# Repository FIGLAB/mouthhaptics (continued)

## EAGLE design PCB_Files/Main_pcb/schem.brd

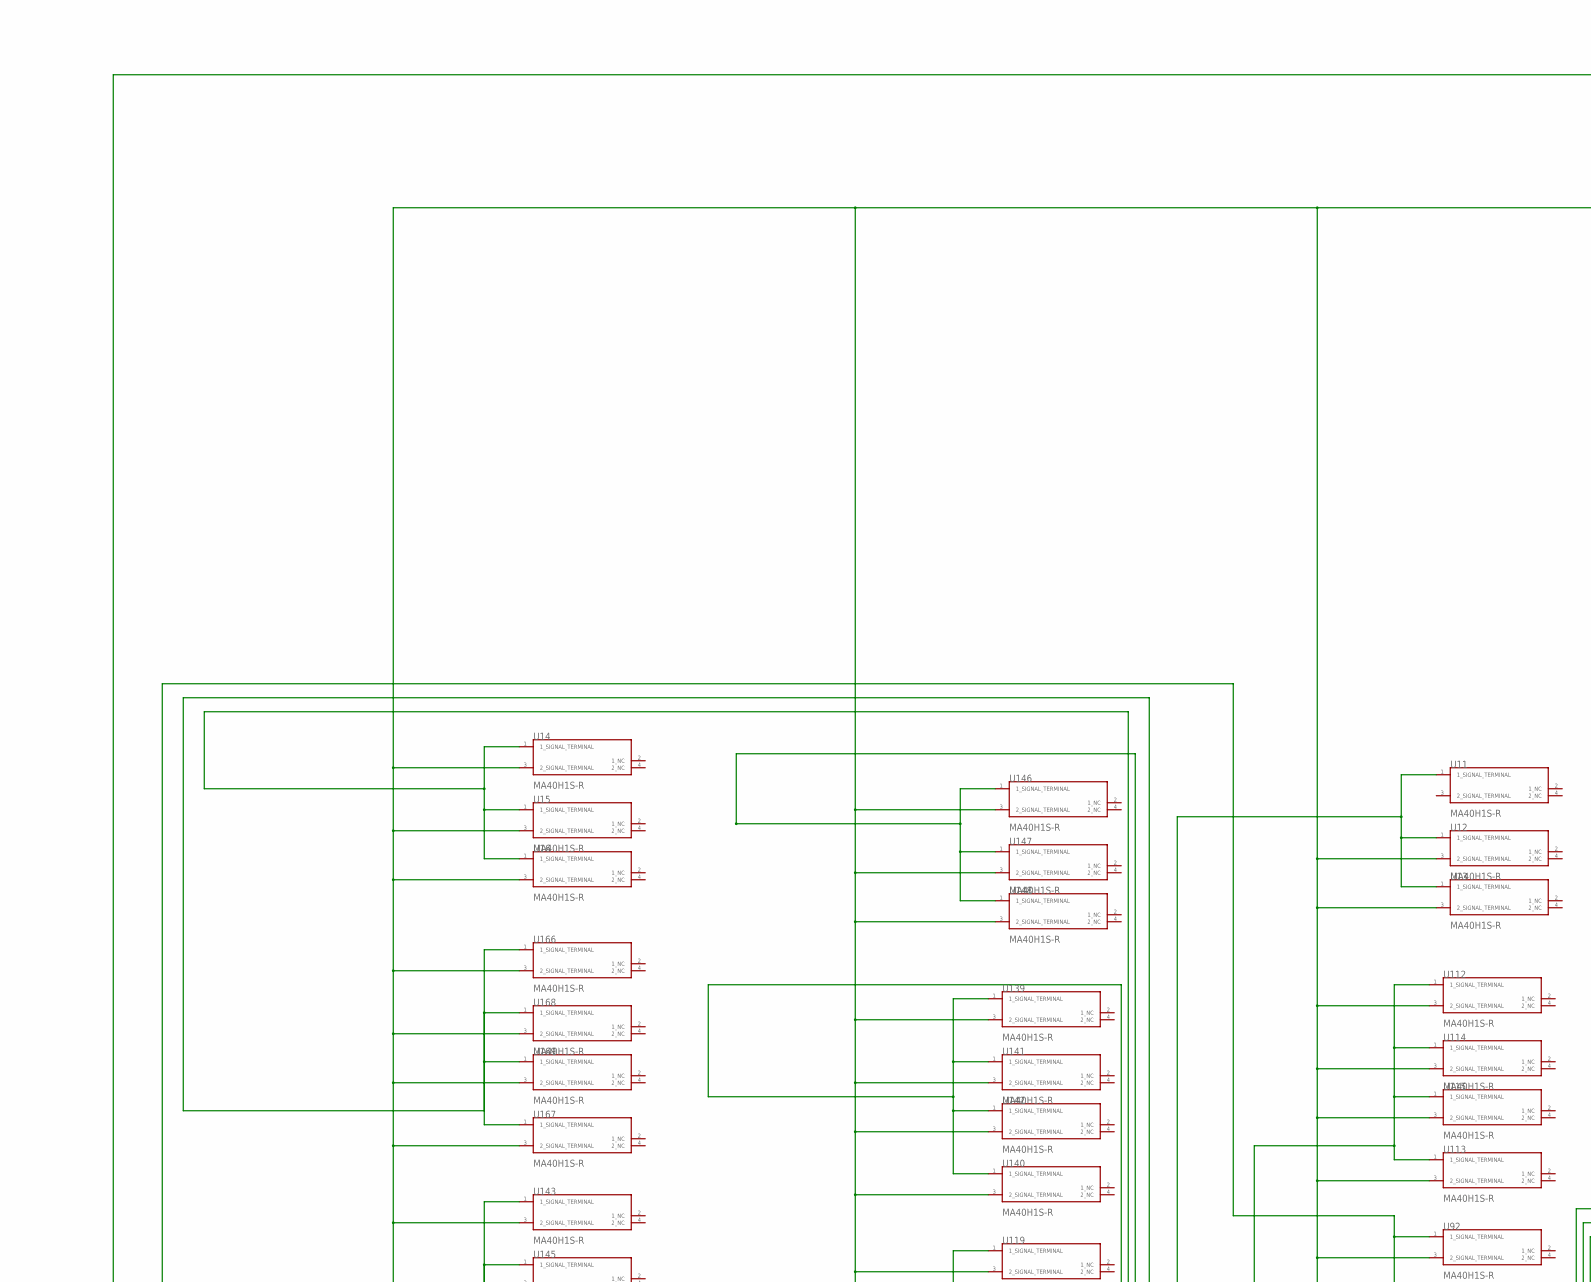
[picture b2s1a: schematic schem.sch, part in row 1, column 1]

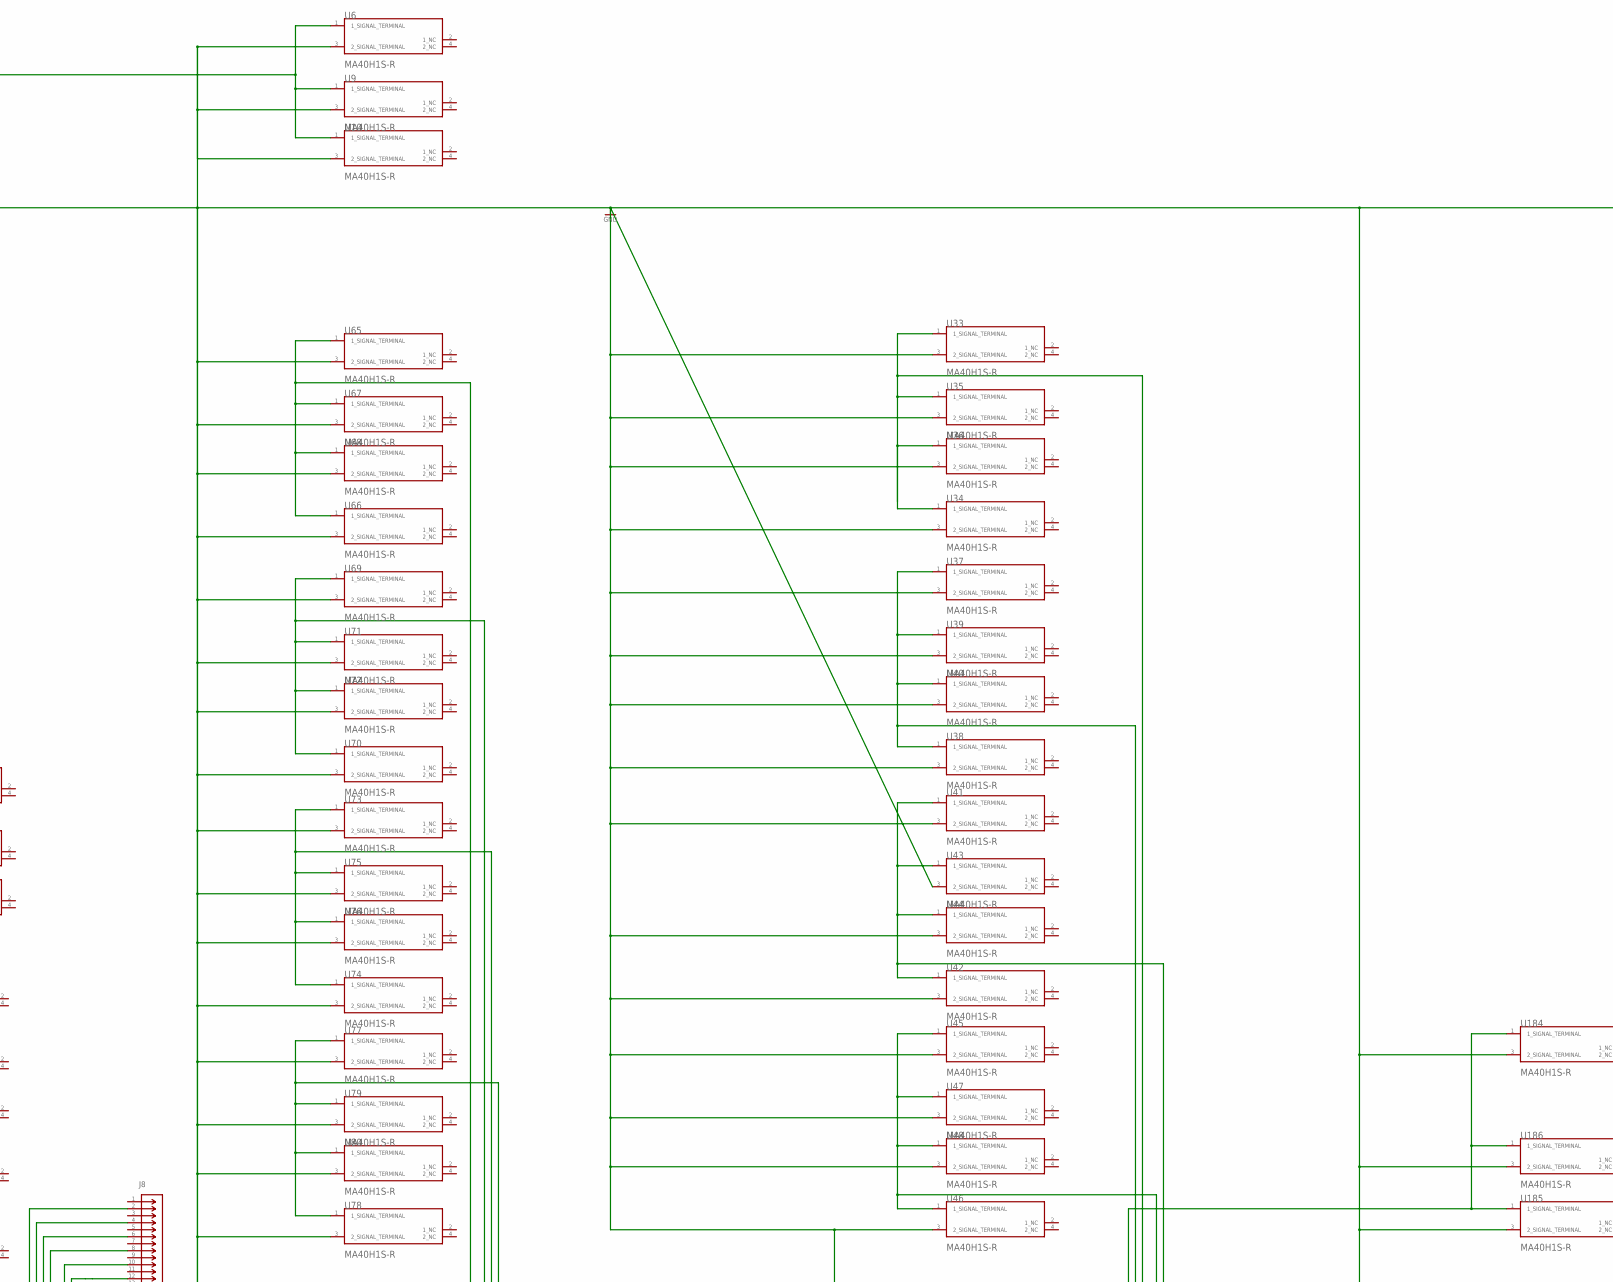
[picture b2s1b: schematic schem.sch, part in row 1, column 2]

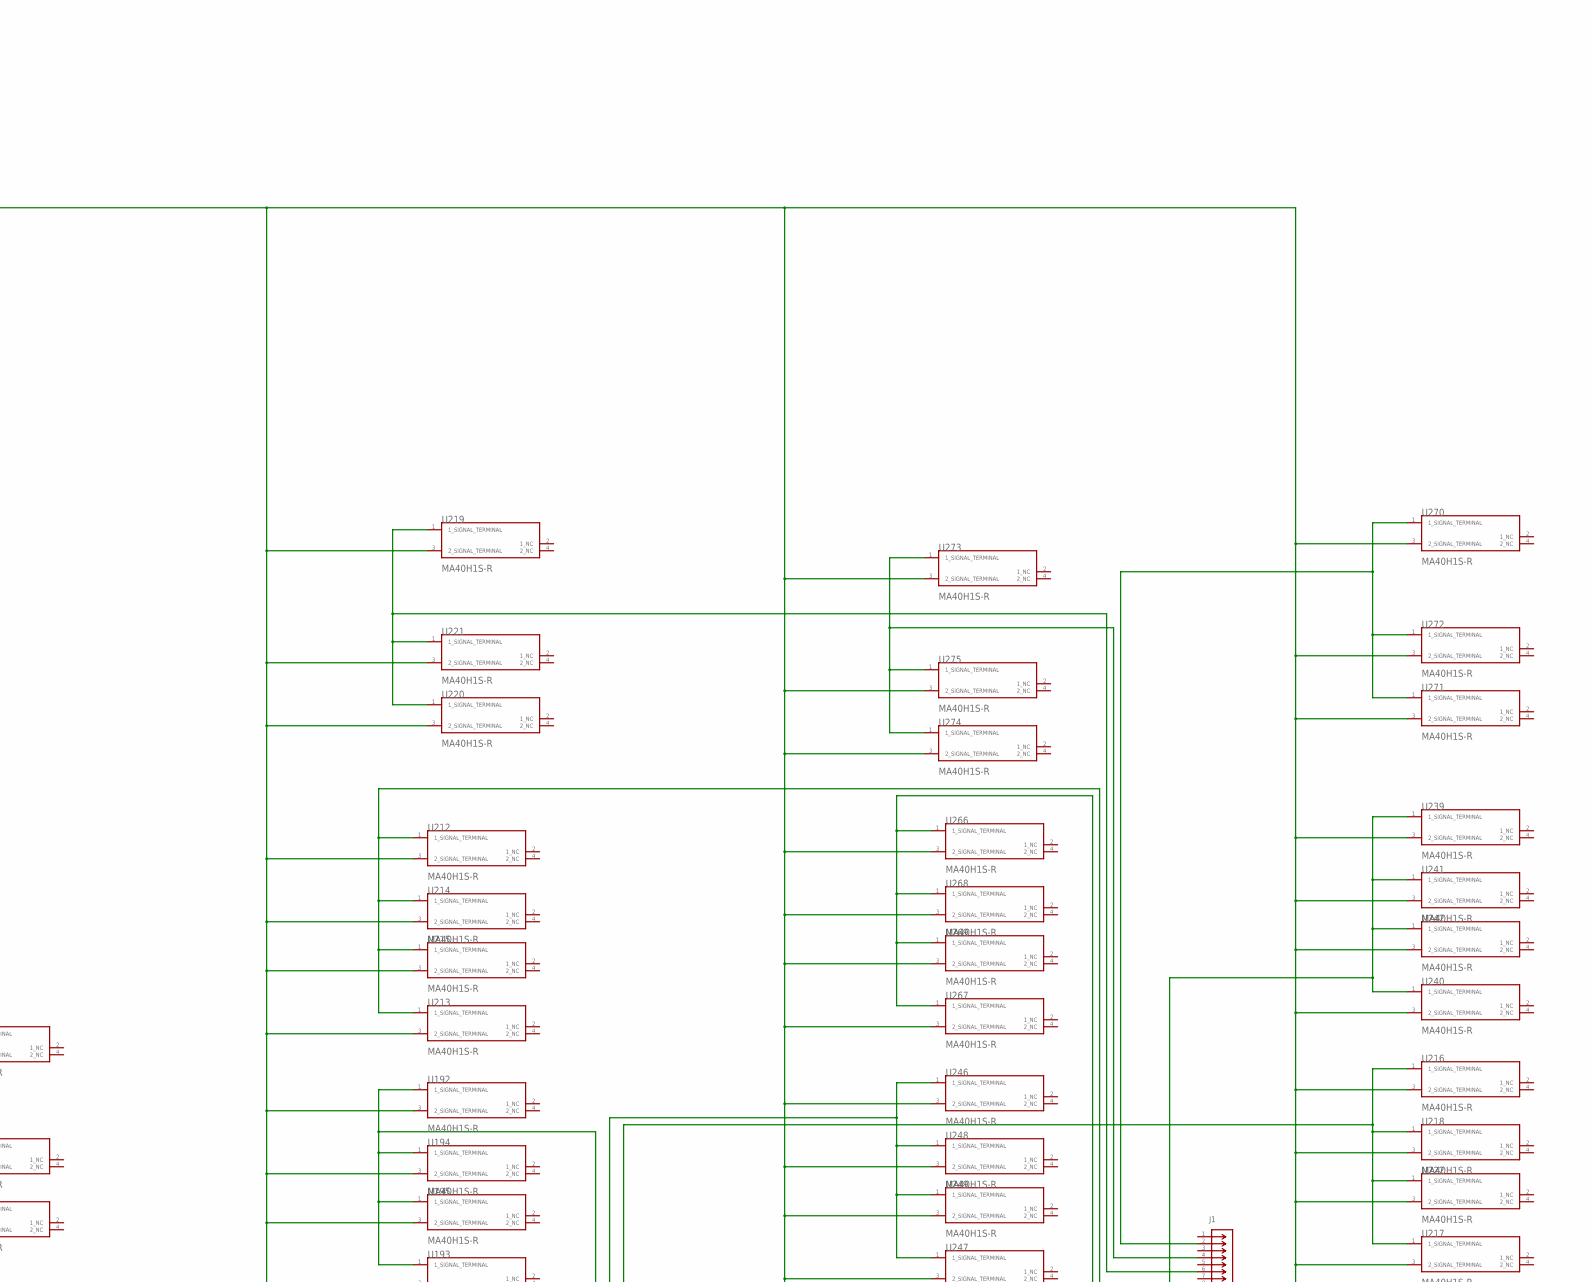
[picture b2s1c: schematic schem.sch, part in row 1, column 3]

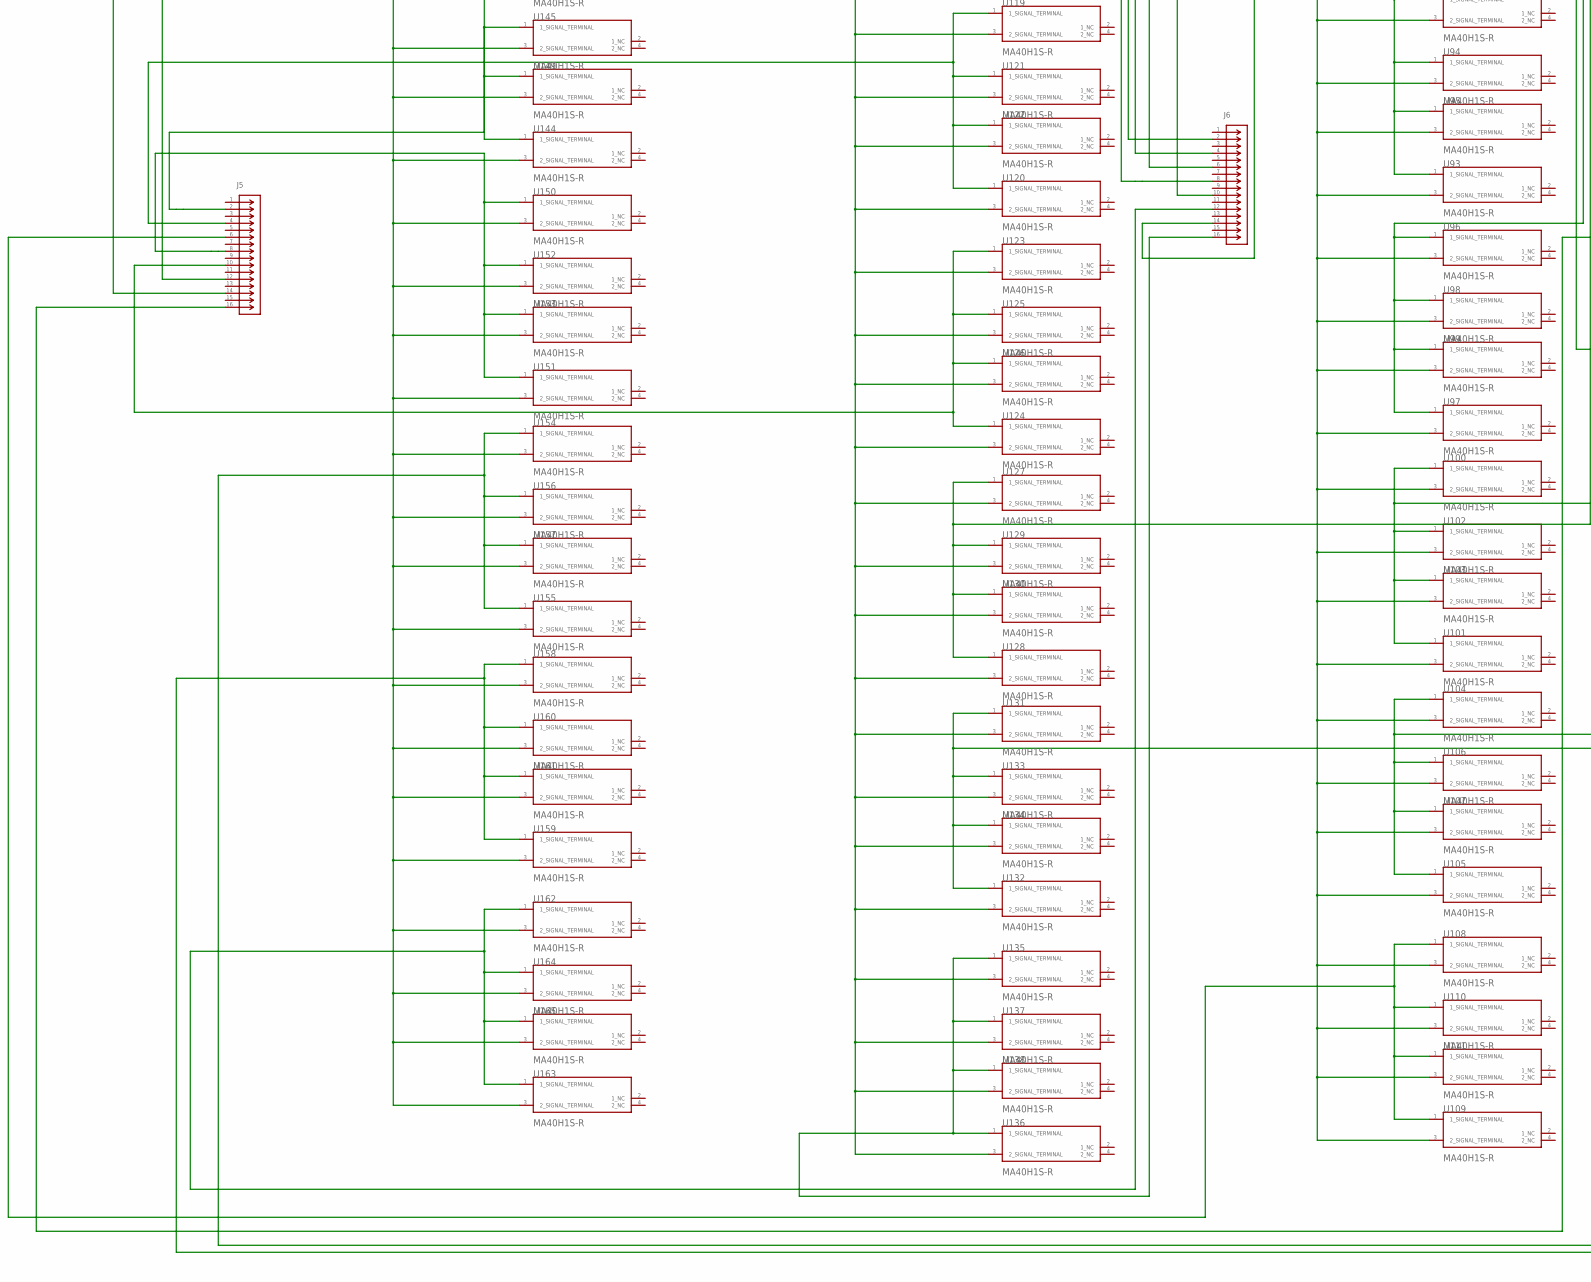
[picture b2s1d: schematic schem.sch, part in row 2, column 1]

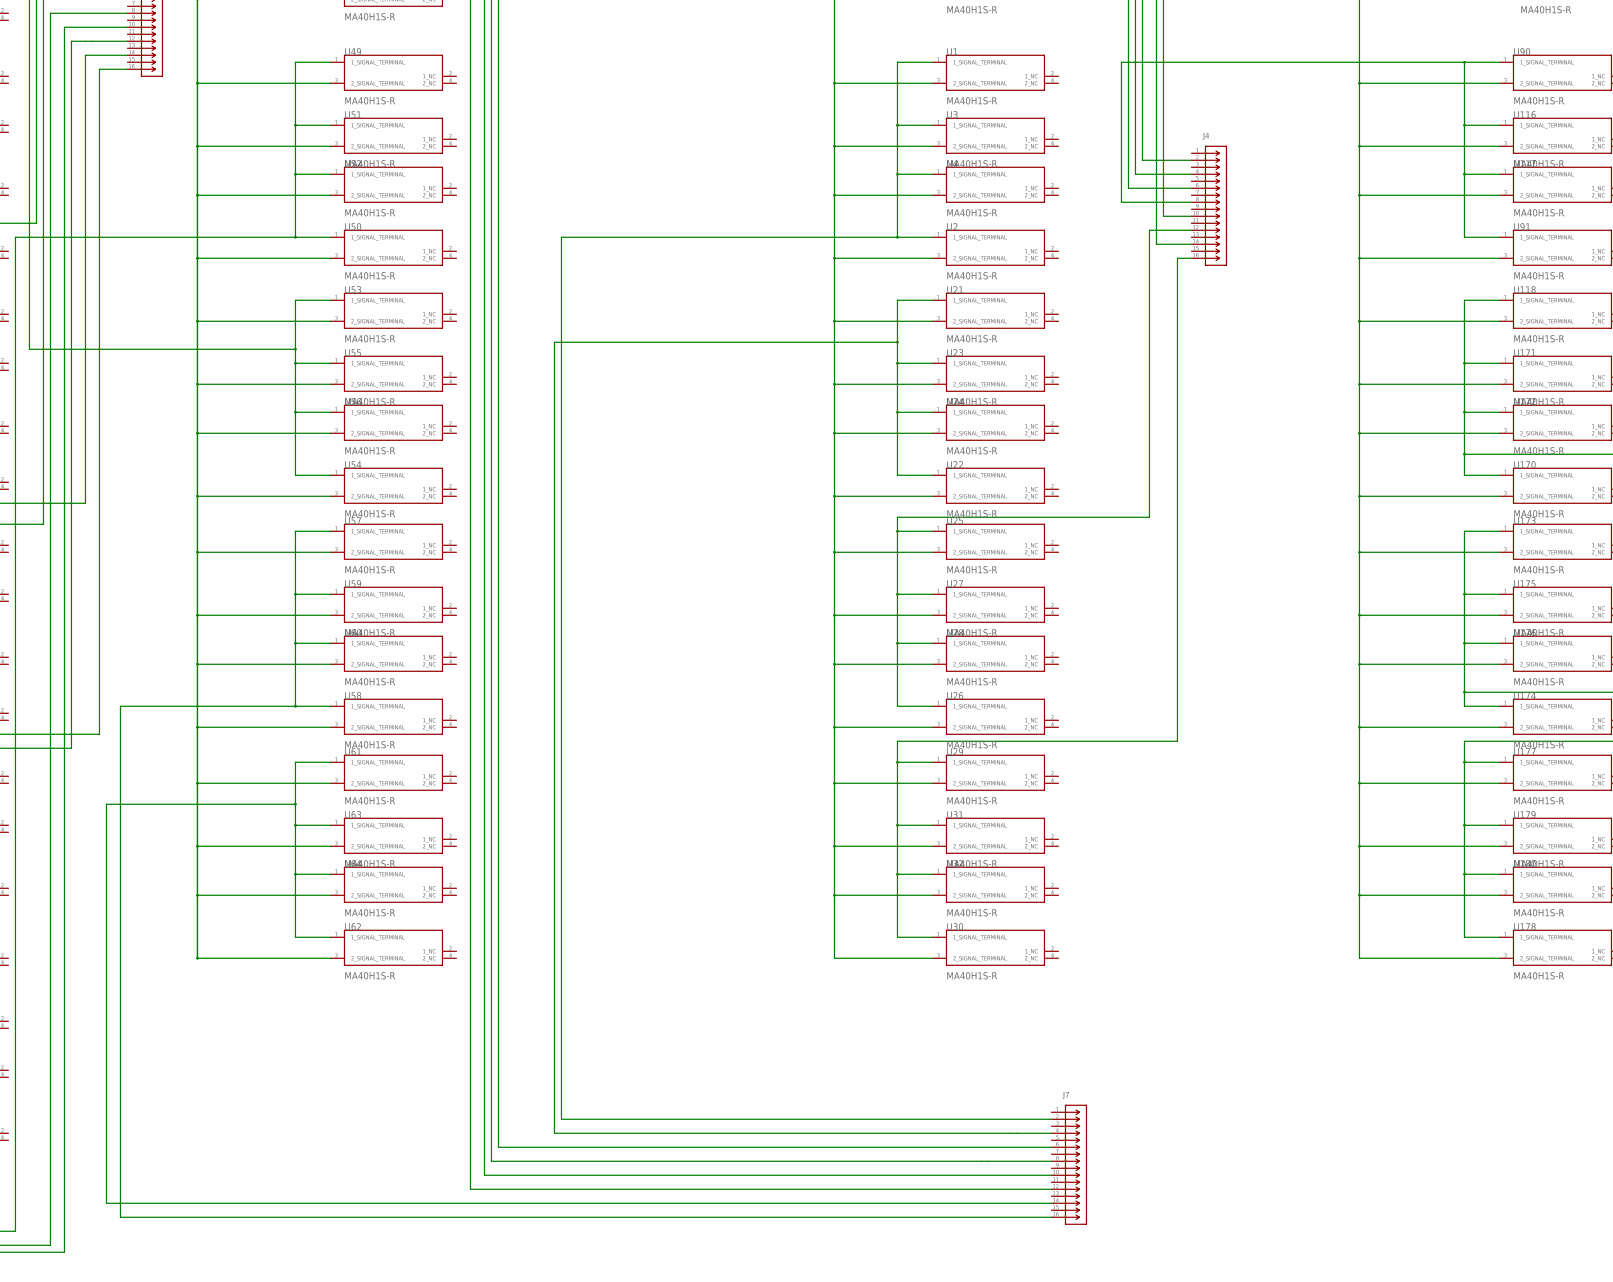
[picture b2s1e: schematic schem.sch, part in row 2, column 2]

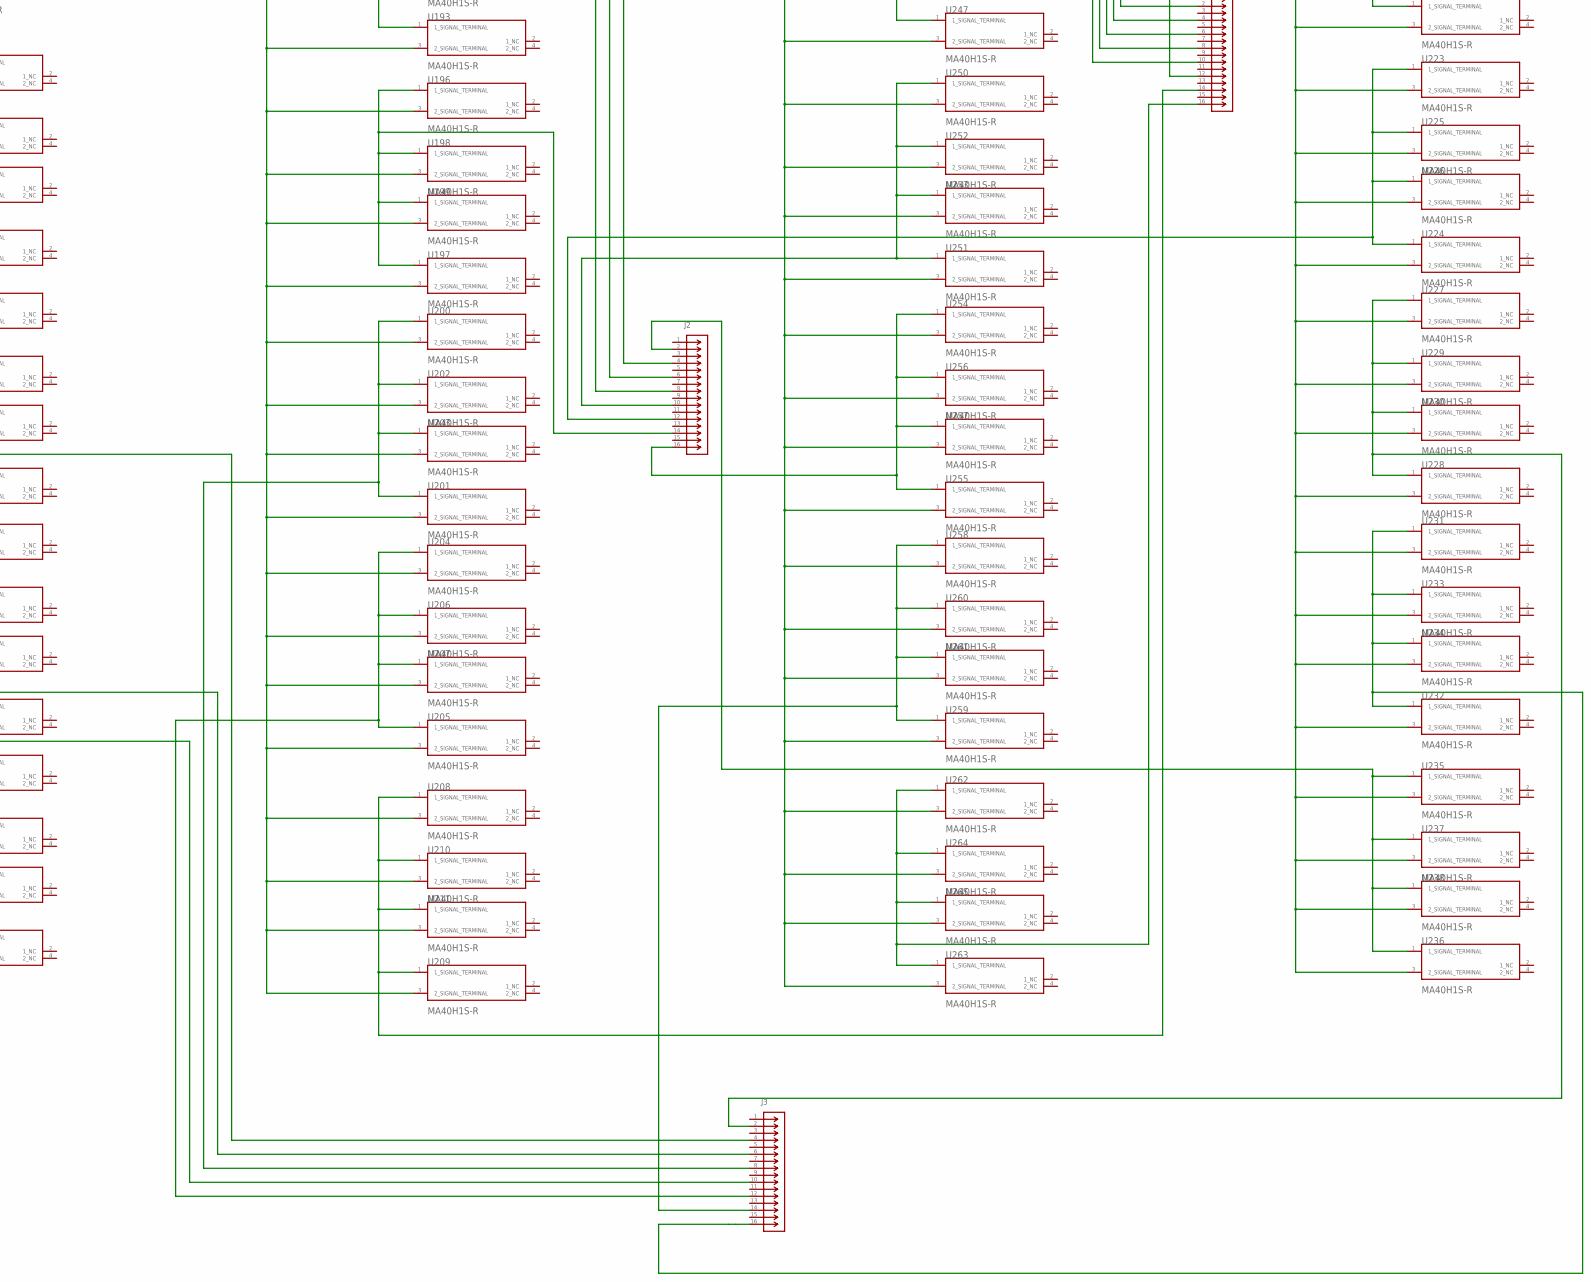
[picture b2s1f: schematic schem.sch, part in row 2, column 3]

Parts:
J1, J2, J3, J4, J5, J6, J7, J8: 70246-1201; CONN_70246-1201_MOL
U1, U2, U3, U4, U6, U9, U10, U11, U12, U13, U14, U15, U16, U21, U22, U23, U24, U25, U26, U27, U28, U29, U30, U31, U32, U33, U34, U35, U36, U37, U38, U39, U40, U41, U42, U43, U44, U45, U46, U47, U48, U49, U50, U51, U52, U53, U54, U55, U56, U57, U58, U59, U60, U61, U62, U63, U64, U65, U66, U67, U68, U69, U70, U71, U72, U73, U74, U75, U76, U77, U78, U79, U80, U90, U91, U92, U93, U94, U95, U96, U97, U98, U99, U100, U101, U102, U103, U104, U105, U106, U107, U108, U109, U110, U111, U112, U113, U114, U115, U116, U117, U118, U119, U120, U121, U122, U123, U124, U125, U126, U127, U128, U129, U130, U131, U132, U133, U134, U135, U136, U137, U138, U139, U140, U141, U142, U143, U144, U145, U146, U147, U148, U149, U150, U151, U152, U153, U154, U155, U156, U157, U158, U159, U160, U161, U162, U163, U164, U165, U166, U167, U168, U169, U170, U171, U172, U173, U174, U175, U176, U177, U178, U179, U180, U184, U185, U186, U192, U193, U194, U195, U196, U197, U198, U199, U200, U201, U202, U203, U204, U205, U206, U207, U208, U209, U210, U211, U212, U213, U214, U215, U216, U217, U218, U219, U220, U221, U222, U223, U224, U225, U226, U227, U228, U229, U230, U231, U232, U233, U234, U235, U236, U237, U238, U239, U240, U241, U242, U246, U247, U248, U249, U250, U251, U252, U253, U254, U255, U256, U257, U258, U259, U260, U261, U262, U263, U264, U265, U266, U267, U268, U269, U270, U271, U272, U273, U274, U275: MURATA_MA40H1S-RMURATA_MA40H1S-R_0_0; MURATA_MA40H1S-R_0

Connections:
GND: U1.3 (2_SIGNAL_TERMINAL), U2.3 (2_SIGNAL_TERMINAL), U3.3 (2_SIGNAL_TERMINAL), U4.3 (2_SIGNAL_TERMINAL), U6.3 (2_SIGNAL_TERMINAL), U9.3 (2_SIGNAL_TERMINAL), U10.3 (2_SIGNAL_TERMINAL), U12.3 (2_SIGNAL_TERMINAL), U13.3 (2_SIGNAL_TERMINAL), U14.3 (2_SIGNAL_TERMINAL), U15.3 (2_SIGNAL_TERMINAL), U16.3 (2_SIGNAL_TERMINAL), U21.3 (2_SIGNAL_TERMINAL), U22.3 (2_SIGNAL_TERMINAL), U23.3 (2_SIGNAL_TERMINAL), U24.3 (2_SIGNAL_TERMINAL), U25.3 (2_SIGNAL_TERMINAL), U26.3 (2_SIGNAL_TERMINAL), U27.3 (2_SIGNAL_TERMINAL), U28.3 (2_SIGNAL_TERMINAL), U29.3 (2_SIGNAL_TERMINAL), U30.3 (2_SIGNAL_TERMINAL), U31.3 (2_SIGNAL_TERMINAL), U32.3 (2_SIGNAL_TERMINAL), U33.3 (2_SIGNAL_TERMINAL), U34.3 (2_SIGNAL_TERMINAL), U35.3 (2_SIGNAL_TERMINAL), U36.3 (2_SIGNAL_TERMINAL), U37.3 (2_SIGNAL_TERMINAL), U38.3 (2_SIGNAL_TERMINAL), U39.3 (2_SIGNAL_TERMINAL), U40.3 (2_SIGNAL_TERMINAL), U41.3 (2_SIGNAL_TERMINAL), U42.3 (2_SIGNAL_TERMINAL), U43.3 (2_SIGNAL_TERMINAL), U44.3 (2_SIGNAL_TERMINAL), U45.3 (2_SIGNAL_TERMINAL), U46.3 (2_SIGNAL_TERMINAL), U47.3 (2_SIGNAL_TERMINAL), U48.3 (2_SIGNAL_TERMINAL), U49.3 (2_SIGNAL_TERMINAL), U50.3 (2_SIGNAL_TERMINAL), U51.3 (2_SIGNAL_TERMINAL), U52.3 (2_SIGNAL_TERMINAL), U53.3 (2_SIGNAL_TERMINAL), U54.3 (2_SIGNAL_TERMINAL), U55.3 (2_SIGNAL_TERMINAL), U56.3 (2_SIGNAL_TERMINAL), U57.3 (2_SIGNAL_TERMINAL), U58.3 (2_SIGNAL_TERMINAL), U59.3 (2_SIGNAL_TERMINAL), U60.3 (2_SIGNAL_TERMINAL), U61.3 (2_SIGNAL_TERMINAL), U62.3 (2_SIGNAL_TERMINAL), U63.3 (2_SIGNAL_TERMINAL), U64.3 (2_SIGNAL_TERMINAL), U65.3 (2_SIGNAL_TERMINAL), U66.3 (2_SIGNAL_TERMINAL), U67.3 (2_SIGNAL_TERMINAL), U68.3 (2_SIGNAL_TERMINAL), U69.3 (2_SIGNAL_TERMINAL), U70.3 (2_SIGNAL_TERMINAL), U71.3 (2_SIGNAL_TERMINAL), U72.3 (2_SIGNAL_TERMINAL), U73.3 (2_SIGNAL_TERMINAL), U74.3 (2_SIGNAL_TERMINAL), U75.3 (2_SIGNAL_TERMINAL), U76.3 (2_SIGNAL_TERMINAL), U77.3 (2_SIGNAL_TERMINAL), U78.3 (2_SIGNAL_TERMINAL), U79.3 (2_SIGNAL_TERMINAL), U80.3 (2_SIGNAL_TERMINAL), U90.3 (2_SIGNAL_TERMINAL), U91.3 (2_SIGNAL_TERMINAL), U92.3 (2_SIGNAL_TERMINAL), U93.3 (2_SIGNAL_TERMINAL), U94.3 (2_SIGNAL_TERMINAL), U95.3 (2_SIGNAL_TERMINAL), U96.3 (2_SIGNAL_TERMINAL), U97.3 (2_SIGNAL_TERMINAL), U98.3 (2_SIGNAL_TERMINAL), U99.3 (2_SIGNAL_TERMINAL), U100.3 (2_SIGNAL_TERMINAL), U101.3 (2_SIGNAL_TERMINAL), U102.3 (2_SIGNAL_TERMINAL), U103.3 (2_SIGNAL_TERMINAL), U104.3 (2_SIGNAL_TERMINAL), U105.3 (2_SIGNAL_TERMINAL), U106.3 (2_SIGNAL_TERMINAL), U107.3 (2_SIGNAL_TERMINAL), U108.3 (2_SIGNAL_TERMINAL), U109.3 (2_SIGNAL_TERMINAL), U110.3 (2_SIGNAL_TERMINAL), U111.3 (2_SIGNAL_TERMINAL), U112.3 (2_SIGNAL_TERMINAL), U113.3 (2_SIGNAL_TERMINAL), U114.3 (2_SIGNAL_TERMINAL), U115.3 (2_SIGNAL_TERMINAL), U116.3 (2_SIGNAL_TERMINAL), U117.3 (2_SIGNAL_TERMINAL), U118.3 (2_SIGNAL_TERMINAL), U119.3 (2_SIGNAL_TERMINAL), U120.3 (2_SIGNAL_TERMINAL), U121.3 (2_SIGNAL_TERMINAL), U122.3 (2_SIGNAL_TERMINAL), U123.3 (2_SIGNAL_TERMINAL), U124.3 (2_SIGNAL_TERMINAL), U125.3 (2_SIGNAL_TERMINAL), U126.3 (2_SIGNAL_TERMINAL), U127.3 (2_SIGNAL_TERMINAL), U128.3 (2_SIGNAL_TERMINAL), U129.3 (2_SIGNAL_TERMINAL), U130.3 (2_SIGNAL_TERMINAL), U131.3 (2_SIGNAL_TERMINAL), U132.3 (2_SIGNAL_TERMINAL), U133.3 (2_SIGNAL_TERMINAL), U134.3 (2_SIGNAL_TERMINAL), U135.3 (2_SIGNAL_TERMINAL), U136.3 (2_SIGNAL_TERMINAL), U137.3 (2_SIGNAL_TERMINAL), U138.3 (2_SIGNAL_TERMINAL), U139.3 (2_SIGNAL_TERMINAL), U140.3 (2_SIGNAL_TERMINAL), U141.3 (2_SIGNAL_TERMINAL), U142.3 (2_SIGNAL_TERMINAL), U143.3 (2_SIGNAL_TERMINAL), U144.3 (2_SIGNAL_TERMINAL), U145.3 (2_SIGNAL_TERMINAL), U146.3 (2_SIGNAL_TERMINAL), U147.3 (2_SIGNAL_TERMINAL), U148.3 (2_SIGNAL_TERMINAL), U149.3 (2_SIGNAL_TERMINAL), U150.3 (2_SIGNAL_TERMINAL), U151.3 (2_SIGNAL_TERMINAL), U152.3 (2_SIGNAL_TERMINAL), U153.3 (2_SIGNAL_TERMINAL), U154.3 (2_SIGNAL_TERMINAL), U155.3 (2_SIGNAL_TERMINAL), U156.3 (2_SIGNAL_TERMINAL), U157.3 (2_SIGNAL_TERMINAL), U158.3 (2_SIGNAL_TERMINAL), U159.3 (2_SIGNAL_TERMINAL), U160.3 (2_SIGNAL_TERMINAL), U161.3 (2_SIGNAL_TERMINAL), U162.3 (2_SIGNAL_TERMINAL), U163.3 (2_SIGNAL_TERMINAL), U164.3 (2_SIGNAL_TERMINAL), U165.3 (2_SIGNAL_TERMINAL), U166.3 (2_SIGNAL_TERMINAL), U167.3 (2_SIGNAL_TERMINAL), U168.3 (2_SIGNAL_TERMINAL), U169.3 (2_SIGNAL_TERMINAL), U170.3 (2_SIGNAL_TERMINAL), U171.3 (2_SIGNAL_TERMINAL), U172.3 (2_SIGNAL_TERMINAL), U173.3 (2_SIGNAL_TERMINAL), U174.3 (2_SIGNAL_TERMINAL), U175.3 (2_SIGNAL_TERMINAL), U176.3 (2_SIGNAL_TERMINAL), U177.3 (2_SIGNAL_TERMINAL), U178.3 (2_SIGNAL_TERMINAL), U179.3 (2_SIGNAL_TERMINAL), U180.3 (2_SIGNAL_TERMINAL), U184.3 (2_SIGNAL_TERMINAL), U185.3 (2_SIGNAL_TERMINAL), U186.3 (2_SIGNAL_TERMINAL), U192.3 (2_SIGNAL_TERMINAL), U193.3 (2_SIGNAL_TERMINAL), U194.3 (2_SIGNAL_TERMINAL), U195.3 (2_SIGNAL_TERMINAL), U196.3 (2_SIGNAL_TERMINAL), U197.3 (2_SIGNAL_TERMINAL), U198.3 (2_SIGNAL_TERMINAL), U199.3 (2_SIGNAL_TERMINAL), U200.3 (2_SIGNAL_TERMINAL), U201.3 (2_SIGNAL_TERMINAL), U202.3 (2_SIGNAL_TERMINAL), U203.3 (2_SIGNAL_TERMINAL), U204.3 (2_SIGNAL_TERMINAL), U205.3 (2_SIGNAL_TERMINAL), U206.3 (2_SIGNAL_TERMINAL), U207.3 (2_SIGNAL_TERMINAL), U208.3 (2_SIGNAL_TERMINAL), U209.3 (2_SIGNAL_TERMINAL), U210.3 (2_SIGNAL_TERMINAL), U211.3 (2_SIGNAL_TERMINAL), U212.3 (2_SIGNAL_TERMINAL), U213.3 (2_SIGNAL_TERMINAL), U214.3 (2_SIGNAL_TERMINAL), U215.3 (2_SIGNAL_TERMINAL), U216.3 (2_SIGNAL_TERMINAL), U217.3 (2_SIGNAL_TERMINAL), U218.3 (2_SIGNAL_TERMINAL), U219.3 (2_SIGNAL_TERMINAL), U220.3 (2_SIGNAL_TERMINAL), U221.3 (2_SIGNAL_TERMINAL), U222.3 (2_SIGNAL_TERMINAL), U223.3 (2_SIGNAL_TERMINAL), U224.3 (2_SIGNAL_TERMINAL), U225.3 (2_SIGNAL_TERMINAL), U226.3 (2_SIGNAL_TERMINAL), U227.3 (2_SIGNAL_TERMINAL), U228.3 (2_SIGNAL_TERMINAL), U229.3 (2_SIGNAL_TERMINAL), U230.3 (2_SIGNAL_TERMINAL), U231.3 (2_SIGNAL_TERMINAL), U232.3 (2_SIGNAL_TERMINAL), U233.3 (2_SIGNAL_TERMINAL), U234.3 (2_SIGNAL_TERMINAL), U235.3 (2_SIGNAL_TERMINAL), U236.3 (2_SIGNAL_TERMINAL), U237.3 (2_SIGNAL_TERMINAL), U238.3 (2_SIGNAL_TERMINAL), U239.3 (2_SIGNAL_TERMINAL), U240.3 (2_SIGNAL_TERMINAL), U241.3 (2_SIGNAL_TERMINAL), U242.3 (2_SIGNAL_TERMINAL), U246.3 (2_SIGNAL_TERMINAL), U247.3 (2_SIGNAL_TERMINAL), U248.3 (2_SIGNAL_TERMINAL), U249.3 (2_SIGNAL_TERMINAL), U250.3 (2_SIGNAL_TERMINAL), U251.3 (2_SIGNAL_TERMINAL), U252.3 (2_SIGNAL_TERMINAL), U253.3 (2_SIGNAL_TERMINAL), U254.3 (2_SIGNAL_TERMINAL), U255.3 (2_SIGNAL_TERMINAL), U256.3 (2_SIGNAL_TERMINAL), U257.3 (2_SIGNAL_TERMINAL), U258.3 (2_SIGNAL_TERMINAL), U259.3 (2_SIGNAL_TERMINAL), U260.3 (2_SIGNAL_TERMINAL), U261.3 (2_SIGNAL_TERMINAL), U262.3 (2_SIGNAL_TERMINAL), U263.3 (2_SIGNAL_TERMINAL), U264.3 (2_SIGNAL_TERMINAL), U265.3 (2_SIGNAL_TERMINAL), U266.3 (2_SIGNAL_TERMINAL), U267.3 (2_SIGNAL_TERMINAL), U268.3 (2_SIGNAL_TERMINAL), U269.3 (2_SIGNAL_TERMINAL), U270.3 (2_SIGNAL_TERMINAL), U271.3 (2_SIGNAL_TERMINAL), U272.3 (2_SIGNAL_TERMINAL), U273.3 (2_SIGNAL_TERMINAL), U274.3 (2_SIGNAL_TERMINAL), U275.3 (2_SIGNAL_TERMINAL)
unnamed: J7.2, U1.1 (1_SIGNAL_TERMINAL), U2.1 (1_SIGNAL_TERMINAL), U3.1 (1_SIGNAL_TERMINAL), U4.1 (1_SIGNAL_TERMINAL)
unnamed: J5.14, U6.1 (1_SIGNAL_TERMINAL), U9.1 (1_SIGNAL_TERMINAL), U10.1 (1_SIGNAL_TERMINAL)
unnamed: J6.2, U14.1 (1_SIGNAL_TERMINAL), U15.1 (1_SIGNAL_TERMINAL), U16.1 (1_SIGNAL_TERMINAL)
unnamed: J7.4, U21.1 (1_SIGNAL_TERMINAL), U22.1 (1_SIGNAL_TERMINAL), U23.1 (1_SIGNAL_TERMINAL), U24.1 (1_SIGNAL_TERMINAL)
unnamed: J4.12, U25.1 (1_SIGNAL_TERMINAL), U26.1 (1_SIGNAL_TERMINAL), U27.1 (1_SIGNAL_TERMINAL), U28.1 (1_SIGNAL_TERMINAL)
unnamed: J4.16, U29.1 (1_SIGNAL_TERMINAL), U30.1 (1_SIGNAL_TERMINAL), U31.1 (1_SIGNAL_TERMINAL), U32.1 (1_SIGNAL_TERMINAL)
unnamed: J4.2, U33.1 (1_SIGNAL_TERMINAL), U34.1 (1_SIGNAL_TERMINAL), U35.1 (1_SIGNAL_TERMINAL), U36.1 (1_SIGNAL_TERMINAL)
unnamed: J4.10, U41.1 (1_SIGNAL_TERMINAL), U42.1 (1_SIGNAL_TERMINAL), U43.1 (1_SIGNAL_TERMINAL), U44.1 (1_SIGNAL_TERMINAL)
unnamed: J4.4, U37.1 (1_SIGNAL_TERMINAL), U38.1 (1_SIGNAL_TERMINAL), U39.1 (1_SIGNAL_TERMINAL), U40.1 (1_SIGNAL_TERMINAL)
unnamed: J4.14, U45.1 (1_SIGNAL_TERMINAL), U46.1 (1_SIGNAL_TERMINAL), U47.1 (1_SIGNAL_TERMINAL), U48.1 (1_SIGNAL_TERMINAL)
unnamed: J5.16, U49.1 (1_SIGNAL_TERMINAL), U50.1 (1_SIGNAL_TERMINAL), U51.1 (1_SIGNAL_TERMINAL), U52.1 (1_SIGNAL_TERMINAL)
unnamed: J8.2, U53.1 (1_SIGNAL_TERMINAL), U54.1 (1_SIGNAL_TERMINAL), U55.1 (1_SIGNAL_TERMINAL), U56.1 (1_SIGNAL_TERMINAL)
unnamed: J7.16, U57.1 (1_SIGNAL_TERMINAL), U58.1 (1_SIGNAL_TERMINAL), U59.1 (1_SIGNAL_TERMINAL), U60.1 (1_SIGNAL_TERMINAL)
unnamed: J7.14, U61.1 (1_SIGNAL_TERMINAL), U62.1 (1_SIGNAL_TERMINAL), U63.1 (1_SIGNAL_TERMINAL), U64.1 (1_SIGNAL_TERMINAL)
unnamed: J7.10, U69.1 (1_SIGNAL_TERMINAL), U70.1 (1_SIGNAL_TERMINAL), U71.1 (1_SIGNAL_TERMINAL), U72.1 (1_SIGNAL_TERMINAL)
unnamed: J6.10, U11.1 (1_SIGNAL_TERMINAL), U12.1 (1_SIGNAL_TERMINAL), U13.1 (1_SIGNAL_TERMINAL)
unnamed: J7.6, U77.1 (1_SIGNAL_TERMINAL), U78.1 (1_SIGNAL_TERMINAL), U79.1 (1_SIGNAL_TERMINAL), U80.1 (1_SIGNAL_TERMINAL)
unnamed: J5.12, U92.1 (1_SIGNAL_TERMINAL), U93.1 (1_SIGNAL_TERMINAL), U94.1 (1_SIGNAL_TERMINAL), U95.1 (1_SIGNAL_TERMINAL)
unnamed: J8.4, U96.1 (1_SIGNAL_TERMINAL), U97.1 (1_SIGNAL_TERMINAL), U98.1 (1_SIGNAL_TERMINAL), U99.1 (1_SIGNAL_TERMINAL)
unnamed: J8.14, U100.1 (1_SIGNAL_TERMINAL), U101.1 (1_SIGNAL_TERMINAL), U102.1 (1_SIGNAL_TERMINAL), U103.1 (1_SIGNAL_TERMINAL)
unnamed: J8.16, U104.1 (1_SIGNAL_TERMINAL), U105.1 (1_SIGNAL_TERMINAL), U106.1 (1_SIGNAL_TERMINAL), U107.1 (1_SIGNAL_TERMINAL)
unnamed: J5.6, U108.1 (1_SIGNAL_TERMINAL), U109.1 (1_SIGNAL_TERMINAL), U110.1 (1_SIGNAL_TERMINAL), U111.1 (1_SIGNAL_TERMINAL)
unnamed: J6.14, U112.1 (1_SIGNAL_TERMINAL), U113.1 (1_SIGNAL_TERMINAL), U114.1 (1_SIGNAL_TERMINAL), U115.1 (1_SIGNAL_TERMINAL)
unnamed: J4.8, U90.1 (1_SIGNAL_TERMINAL), U91.1 (1_SIGNAL_TERMINAL), U116.1 (1_SIGNAL_TERMINAL), U117.1 (1_SIGNAL_TERMINAL)
unnamed: J5.4, U119.1 (1_SIGNAL_TERMINAL), U120.1 (1_SIGNAL_TERMINAL), U121.1 (1_SIGNAL_TERMINAL), U122.1 (1_SIGNAL_TERMINAL)
unnamed: J5.10, U123.1 (1_SIGNAL_TERMINAL), U124.1 (1_SIGNAL_TERMINAL), U125.1 (1_SIGNAL_TERMINAL), U126.1 (1_SIGNAL_TERMINAL)
unnamed: J8.6, U127.1 (1_SIGNAL_TERMINAL), U128.1 (1_SIGNAL_TERMINAL), U129.1 (1_SIGNAL_TERMINAL), U130.1 (1_SIGNAL_TERMINAL)
unnamed: J8.12, U131.1 (1_SIGNAL_TERMINAL), U132.1 (1_SIGNAL_TERMINAL), U133.1 (1_SIGNAL_TERMINAL), U134.1 (1_SIGNAL_TERMINAL)
unnamed: J6.16, U135.1 (1_SIGNAL_TERMINAL), U136.1 (1_SIGNAL_TERMINAL), U137.1 (1_SIGNAL_TERMINAL), U138.1 (1_SIGNAL_TERMINAL)
unnamed: J6.8, U139.1 (1_SIGNAL_TERMINAL), U140.1 (1_SIGNAL_TERMINAL), U141.1 (1_SIGNAL_TERMINAL), U142.1 (1_SIGNAL_TERMINAL)
unnamed: J5.2, U143.1 (1_SIGNAL_TERMINAL), U144.1 (1_SIGNAL_TERMINAL), U145.1 (1_SIGNAL_TERMINAL), U149.1 (1_SIGNAL_TERMINAL)
unnamed: J6.4, U146.1 (1_SIGNAL_TERMINAL), U147.1 (1_SIGNAL_TERMINAL), U148.1 (1_SIGNAL_TERMINAL)
unnamed: J5.8, U150.1 (1_SIGNAL_TERMINAL), U151.1 (1_SIGNAL_TERMINAL), U152.1 (1_SIGNAL_TERMINAL), U153.1 (1_SIGNAL_TERMINAL)
unnamed: J8.8, U154.1 (1_SIGNAL_TERMINAL), U155.1 (1_SIGNAL_TERMINAL), U156.1 (1_SIGNAL_TERMINAL), U157.1 (1_SIGNAL_TERMINAL)
unnamed: J8.10, U158.1 (1_SIGNAL_TERMINAL), U159.1 (1_SIGNAL_TERMINAL), U160.1 (1_SIGNAL_TERMINAL), U161.1 (1_SIGNAL_TERMINAL)
unnamed: J6.12, U162.1 (1_SIGNAL_TERMINAL), U163.1 (1_SIGNAL_TERMINAL), U164.1 (1_SIGNAL_TERMINAL), U165.1 (1_SIGNAL_TERMINAL)
unnamed: J6.6, U166.1 (1_SIGNAL_TERMINAL), U167.1 (1_SIGNAL_TERMINAL), U168.1 (1_SIGNAL_TERMINAL), U169.1 (1_SIGNAL_TERMINAL)
unnamed: J3.4, U118.1 (1_SIGNAL_TERMINAL), U170.1 (1_SIGNAL_TERMINAL), U171.1 (1_SIGNAL_TERMINAL), U172.1 (1_SIGNAL_TERMINAL)
unnamed: J3.6, U173.1 (1_SIGNAL_TERMINAL), U174.1 (1_SIGNAL_TERMINAL), U175.1 (1_SIGNAL_TERMINAL), U176.1 (1_SIGNAL_TERMINAL)
unnamed: J3.10, U177.1 (1_SIGNAL_TERMINAL), U178.1 (1_SIGNAL_TERMINAL), U179.1 (1_SIGNAL_TERMINAL), U180.1 (1_SIGNAL_TERMINAL)
unnamed: J7.8, U73.1 (1_SIGNAL_TERMINAL), U74.1 (1_SIGNAL_TERMINAL), U75.1 (1_SIGNAL_TERMINAL), U76.1 (1_SIGNAL_TERMINAL)
unnamed: J4.6, U184.1 (1_SIGNAL_TERMINAL), U185.1 (1_SIGNAL_TERMINAL), U186.1 (1_SIGNAL_TERMINAL)
unnamed: J2.8, U192.1 (1_SIGNAL_TERMINAL), U193.1 (1_SIGNAL_TERMINAL), U194.1 (1_SIGNAL_TERMINAL), U195.1 (1_SIGNAL_TERMINAL)
unnamed: J2.14, U196.1 (1_SIGNAL_TERMINAL), U197.1 (1_SIGNAL_TERMINAL), U198.1 (1_SIGNAL_TERMINAL), U199.1 (1_SIGNAL_TERMINAL)
unnamed: J3.8, U200.1 (1_SIGNAL_TERMINAL), U201.1 (1_SIGNAL_TERMINAL), U202.1 (1_SIGNAL_TERMINAL), U203.1 (1_SIGNAL_TERMINAL)
unnamed: J3.12, U204.1 (1_SIGNAL_TERMINAL), U205.1 (1_SIGNAL_TERMINAL), U206.1 (1_SIGNAL_TERMINAL), U207.1 (1_SIGNAL_TERMINAL)
unnamed: J1.14, U208.1 (1_SIGNAL_TERMINAL), U209.1 (1_SIGNAL_TERMINAL), U210.1 (1_SIGNAL_TERMINAL), U211.1 (1_SIGNAL_TERMINAL)
unnamed: J1.8, U212.1 (1_SIGNAL_TERMINAL), U213.1 (1_SIGNAL_TERMINAL), U214.1 (1_SIGNAL_TERMINAL), U215.1 (1_SIGNAL_TERMINAL)
unnamed: J2.4, U216.1 (1_SIGNAL_TERMINAL), U217.1 (1_SIGNAL_TERMINAL), U218.1 (1_SIGNAL_TERMINAL), U222.1 (1_SIGNAL_TERMINAL)
unnamed: J1.6, U219.1 (1_SIGNAL_TERMINAL), U220.1 (1_SIGNAL_TERMINAL), U221.1 (1_SIGNAL_TERMINAL)
unnamed: J2.12, U223.1 (1_SIGNAL_TERMINAL), U224.1 (1_SIGNAL_TERMINAL), U225.1 (1_SIGNAL_TERMINAL), U226.1 (1_SIGNAL_TERMINAL)
unnamed: J3.2, U227.1 (1_SIGNAL_TERMINAL), U228.1 (1_SIGNAL_TERMINAL), U229.1 (1_SIGNAL_TERMINAL), U230.1 (1_SIGNAL_TERMINAL)
unnamed: J3.16, U231.1 (1_SIGNAL_TERMINAL), U232.1 (1_SIGNAL_TERMINAL), U233.1 (1_SIGNAL_TERMINAL), U234.1 (1_SIGNAL_TERMINAL)
unnamed: J2.2, U235.1 (1_SIGNAL_TERMINAL), U236.1 (1_SIGNAL_TERMINAL), U237.1 (1_SIGNAL_TERMINAL), U238.1 (1_SIGNAL_TERMINAL)
unnamed: J1.12, U239.1 (1_SIGNAL_TERMINAL), U240.1 (1_SIGNAL_TERMINAL), U241.1 (1_SIGNAL_TERMINAL), U242.1 (1_SIGNAL_TERMINAL)
unnamed: J2.6, U246.1 (1_SIGNAL_TERMINAL), U247.1 (1_SIGNAL_TERMINAL), U248.1 (1_SIGNAL_TERMINAL), U249.1 (1_SIGNAL_TERMINAL)
unnamed: J2.10, U250.1 (1_SIGNAL_TERMINAL), U251.1 (1_SIGNAL_TERMINAL), U252.1 (1_SIGNAL_TERMINAL), U253.1 (1_SIGNAL_TERMINAL)
unnamed: J2.16, U254.1 (1_SIGNAL_TERMINAL), U255.1 (1_SIGNAL_TERMINAL), U256.1 (1_SIGNAL_TERMINAL), U257.1 (1_SIGNAL_TERMINAL)
unnamed: J3.14, U258.1 (1_SIGNAL_TERMINAL), U259.1 (1_SIGNAL_TERMINAL), U260.1 (1_SIGNAL_TERMINAL), U261.1 (1_SIGNAL_TERMINAL)
unnamed: J1.16, U262.1 (1_SIGNAL_TERMINAL), U263.1 (1_SIGNAL_TERMINAL), U264.1 (1_SIGNAL_TERMINAL), U265.1 (1_SIGNAL_TERMINAL)
unnamed: J1.10, U266.1 (1_SIGNAL_TERMINAL), U267.1 (1_SIGNAL_TERMINAL), U268.1 (1_SIGNAL_TERMINAL), U269.1 (1_SIGNAL_TERMINAL)
unnamed: J1.2, U270.1 (1_SIGNAL_TERMINAL), U271.1 (1_SIGNAL_TERMINAL), U272.1 (1_SIGNAL_TERMINAL)
unnamed: J1.4, U273.1 (1_SIGNAL_TERMINAL), U274.1 (1_SIGNAL_TERMINAL), U275.1 (1_SIGNAL_TERMINAL)
unnamed: J7.12, U65.1 (1_SIGNAL_TERMINAL), U66.1 (1_SIGNAL_TERMINAL), U67.1 (1_SIGNAL_TERMINAL), U68.1 (1_SIGNAL_TERMINAL)

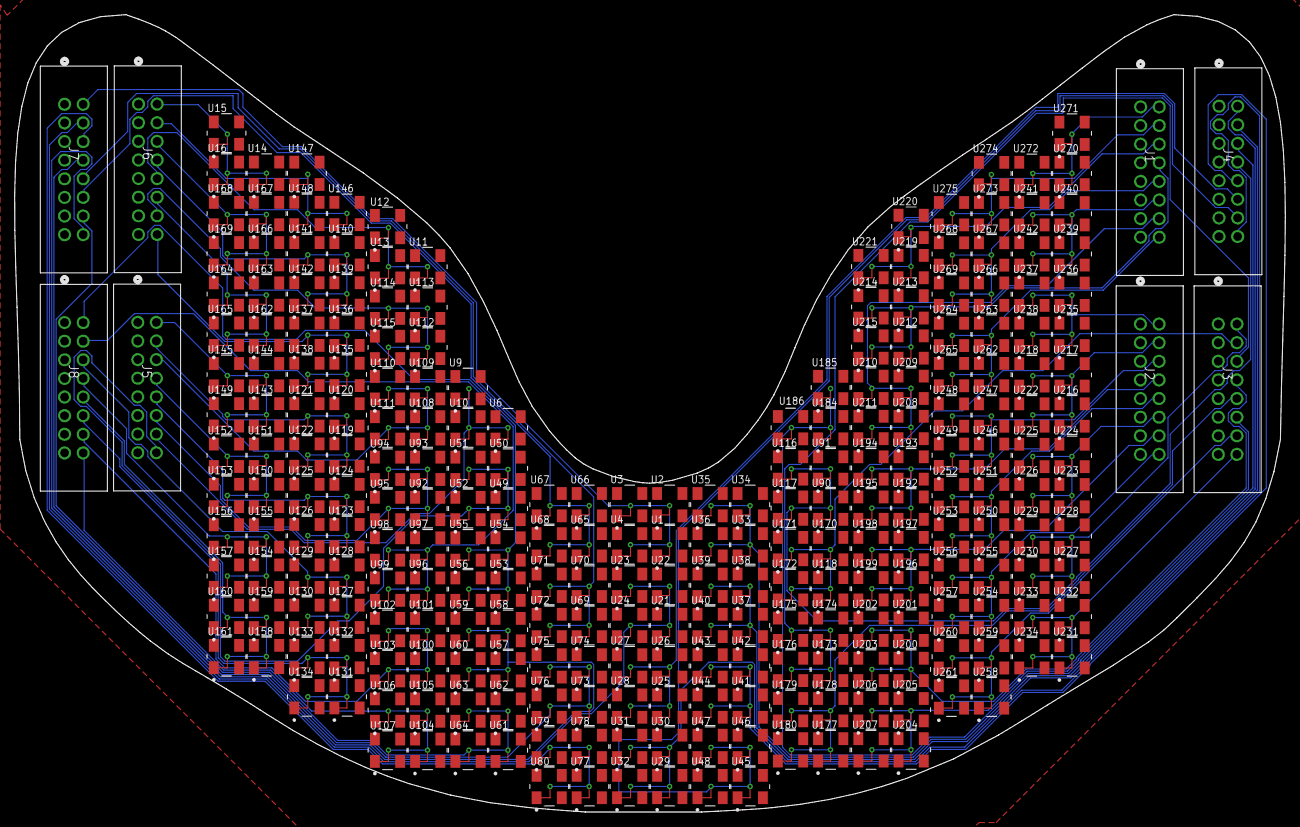
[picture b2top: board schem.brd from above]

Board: 2 copper layers, 173.3 x 108.7 mm, 256 parts (0 on the bottom side), 65 nets.

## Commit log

2022-05-22 Delete LICENSE
    changing
2022-05-22 Create LICENSE.GPL2
    added license at suggestion by cmu
2022-10-26 Finally getting around to cleaning up my repository and open sourcing it
2022-10-26 updating readme
2022-12-01 adding the 3D prints for the spherical cap
2023-05-04 adding unity gitignore
2023-05-05 adding scenes
2023-05-05 adding oculus package
2023-05-05 added project settings
2023-05-05 added scripts
2023-05-05 added XRpackage
2023-05-05 added resources
2023-05-06 addding racecar sssets
2023-05-06 adding materials
2023-05-06 adding sounds
2023-05-06 adding terrain stuff
2023-05-06 everything else
2024-01-18 added main pcb oops
